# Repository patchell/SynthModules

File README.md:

# SynthModules
 Collection of Analog Synthesizer Modules

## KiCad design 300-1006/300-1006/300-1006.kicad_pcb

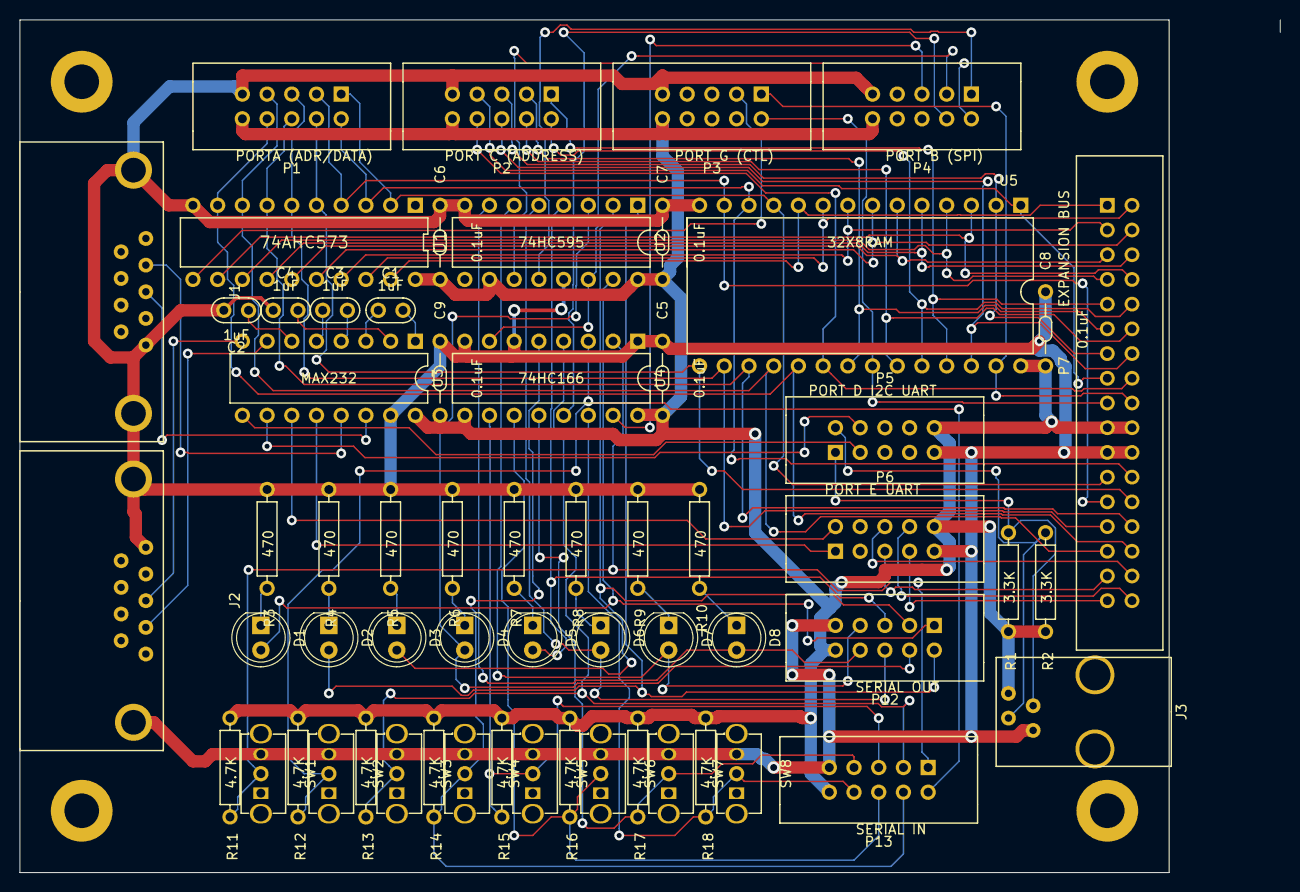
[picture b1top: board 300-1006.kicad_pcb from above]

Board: 2 copper layers, 129.5 x 87.6 mm, 64 parts (0 on the bottom side), 78 nets.

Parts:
C1, C2, C3, C4: 1uF; CAP-0.1
C5, C6, C7, C8, C9: 0.1uF; CAP-Bypass-0_3
D1, D2, D3, D4, D5, D6, D7, D8: LED; LED_5.0mm
J1: RS232 DTE MALE; DSUB-9P
J2: RS232 DCE FEM; DSUB-9S
J3: I2C; RJ9-PCB-Conn
P1: PORTA (ADR/DATA); IDC5x2_Vert
P2: PORT C (ADDRESS); IDC5x2_Vert
P3: PORT G (CTL); IDC5x2_Vert
P4: PORT B (SPI); IDC5x2_Vert
P5: PORT D I2C UART; IDC5x2_Vert
P6: PORT E UART; IDC5x2_Vert
P7: EXPANSION BUS; IDC_17x2
P8, P9, P10, P11: PAD; MountingHole_140
P12: SERIAL OUT; IDC5x2_Vert
P13: SERIAL IN; IDC5x2_Vert
R1, R2: 3.3K; AXIAL0_4
R3, R4, R5, R6, R7, R8, R9, R10: 470; AXIAL0_4
R11, R12, R13, R14, R15, R16, R17, R18: 4.7K; AXIAL0_4
SW1, SW2, SW3, SW4, SW5, SW6, SW7, SW8: SW-SPDT; SWITCH_SPDT-OS102011MS2QN1
U1: 74AHC573; DIP-20.3
U2: 74HC595; DIP-16
U3: MAX232; DIP-16
U4: 74HC166; DIP-16
U5: 32X8RAM; DIP28_6

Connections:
+5V0: C5.1, C6.1, C7.1, C8.1, C9.1, J3.4, P1.10, P2.10, P3.10, P4.10, P5.10, P6.10, P7.19, P7.20, P12.10, P13.10, R1.1, R2.1, R11.2, R12.2, R13.2, R14.2, R15.2, R16.2, R17.2, R18.2, U1.20, U2.10, U2.16, U3.16, U4.9, U4.16, U5.28
/A0: P7.1, U1.19, U5.10
/A1: P7.2, U1.18, U5.9
/A2: P7.3, U1.17, U5.8
/A3: P7.4, U1.16, U5.7
/A4: P7.5, U1.15, U5.6
/A5: P7.6, U1.14, U5.5
/A6: P7.7, U1.13, U5.4
/A7: P7.8, U1.12, U5.3
/A8: P2.1, P7.9, U5.25
/A9: P2.2, P7.10, U5.24
/A10: P2.3, P7.11, U5.21
/A11: P2.4, P7.12, U5.23
/A12: P2.5, P7.13, U5.2
/A13: P2.6, P7.14, U5.26
/A14: P2.7, P7.15, U5.1
/A15: P2.8, P7.16, U5.20
/AD0: P1.1, P7.23, U1.2, U5.11
/AD1: P1.2, P7.24, U1.3, U5.12
/AD2: P1.3, P7.25, U1.4, U5.13
/AD3: P1.4, P7.26, U1.5, U5.15
/AD4: P1.5, P7.27, U1.6, U5.16
/AD5: P1.6, P7.28, U1.7, U5.17
/AD6: P1.7, P7.29, U1.8, U5.18
/AD7: P1.8, P7.30, U1.9, U5.19
/ALE: P3.3, U1.11
/INT4: P6.5, P7.31
/INT5: P6.6, P7.32
/INT6: P6.7, P7.33
/INT7: P6.8, P7.34
/LOAD: P4.1, U2.12
/MISO: P4.4, U4.13
/MOSI: P4.3, U2.14, U4.7
/NRD: P3.2, P7.17, U5.22
/NWR: P3.1, P7.18, U5.27
/RXD0: J1.2, U3.13
/RXD0M: P6.1, U3.12
/RXD1: J2.3, U3.8
/RXD1M: P5.3, U3.9
/SCK: P4.2, U2.11
/SCL: J3.3, P5.1, R1.2
/SDA: J3.2, P5.2, R2.2
/SH_NLD: P4.5, U4.15
/SI0: P13.1, R11.1, SW1.2, U4.2
/SI1: P13.2, R12.1, SW2.2, U4.3
/SI2: P13.3, R13.1, SW3.2, U4.4
/SI3: P13.4, R14.1, SW4.2, U4.5
/SI4: P13.5, R15.1, SW5.2, U4.10
/SI5: P13.6, R16.1, SW6.2, U4.11
/SI6: P13.7, R17.1, SW7.2, U4.12
/SI7: P13.8, R18.1, SW8.2, U4.14
/SO0: D1.2, P12.1, U2.15
/SO1: D2.2, P12.2, U2.1
/SO2: D3.2, P12.3, U2.2
/SO3: D4.2, P12.4, U2.3
/SO4: D5.2, P12.5, U2.4
/SO5: D6.2, P12.6, U2.5
/SO6: D7.2, P12.7, U2.6
/SO7: D8.2, P12.8, U2.7
/TXD0: J1.3, U3.14
/TXD0M: P6.2, U3.11
/TXD1: J2.2, U3.7
/TXD1M: P5.4, U3.10
GND: C2.1, C4.2, C5.2, C6.2, C7.2, C8.2, C9.2, J1.0, J1.5, J2.0, J2.5, J3.1, P1.9, P2.9, P3.9, P4.9, P5.9, P6.9, P7.21, P7.22, P12.9, P13.9, R3.2, R4.2, R5.2, R6.2, R7.2, R8.2, R9.2, R10.2, SW1.3, SW2.3, SW3.3, SW4.3, SW5.3, SW6.3, SW7.3, SW8.3, U1.10, U2.8, U2.13, U3.15, U4.1, U4.6, U4.8, U5.14
unnamed: C1.1, U3.1
unnamed: C1.2, U3.3
unnamed: C2.2, U3.6
unnamed: C3.1, U3.4
unnamed: C3.2, U3.5
unnamed: C4.1, U3.2
unnamed: D1.1, R3.1
unnamed: D2.1, R4.1
unnamed: D3.1, R5.1
unnamed: D4.1, R6.1
unnamed: D5.1, R7.1
unnamed: D6.1, R8.1
unnamed: D7.1, R9.1
unnamed: D8.1, R10.1

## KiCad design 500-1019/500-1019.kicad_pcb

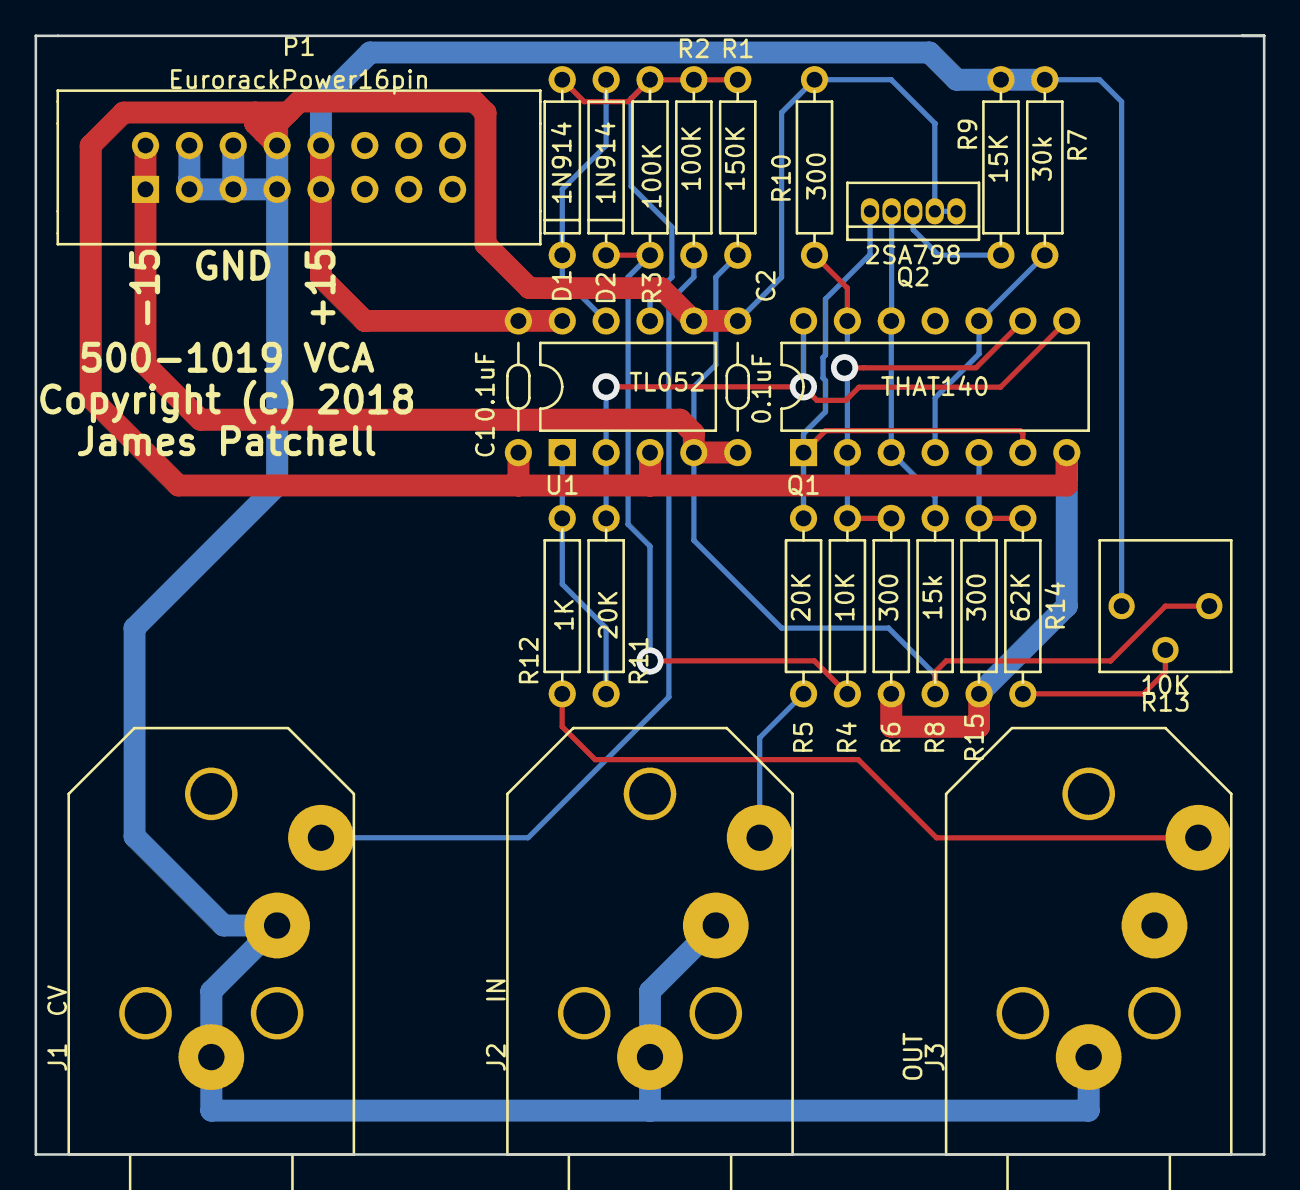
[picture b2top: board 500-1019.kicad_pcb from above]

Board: 2 copper layers, 71.1 x 64.8 mm, 26 parts (0 on the bottom side), 19 nets.

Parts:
C1, C2: 0.1uF; CAP-Bypass-0.3
D1, D2: 1N914; DIODE0.4
J1: CV; PHONE-SC112A
J2: IN; PHONE-SC112A
J3: OUT; PHONE-SC112A
P1: EurorackPower16pin; IDC8x2_Vert
Q1: THAT140; DIP-14.3
Q2: 2SA798
R1: 150K; AXIAL0_4
R2, R3: 100K; AXIAL0_4
R4: 10K; AXIAL0.4
R5, R11: 20K; AXIAL0.4
R6, R10, R15: 300; AXIAL0.4
R7: 30k; AXIAL0.4
R8: 15k; AXIAL0.4
R9: 15K; AXIAL0.4
R12: 1K; AXIAL0.4
R13: 10K; Trimpot
R14: 62K; AXIAL0.4
U1: TL052; DIP8.3

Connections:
+15V0: C1.1, P1.9, P1.10, R7.1, R9.1, R13.1, U1.8
-15V0: C2.1, P1.1, P1.2, R1.2, R8.2, R13.3, U1.4
/Vin: D2.1, R3.1, R4.2
GND: C1.2, C2.2, J1.1, J1.2, J2.1, J2.2, J3.1, P1.3, P1.4, P1.5, P1.6, P1.7, P1.8, Q1.7, Q2.4, Q2.5, R6.2, R10.2, R15.2, U1.3, U1.5
unnamed: D1.1, D2.2, U1.7
unnamed: D1.2, R1.1, R2.1, R3.2, U1.6
unnamed: J1.3, R2.2
unnamed: J2.3, R5.2
unnamed: J3.3, R12.1
unnamed: Q1.1, Q1.6, Q2.1, R5.1
unnamed: Q1.2, Q1.9, R4.1, R6.1
unnamed: Q1.5, R14.1, R15.1
unnamed: Q1.4, Q1.10, R7.2
unnamed: Q1.3, Q1.12, Q2.2, R8.1
unnamed: Q1.13, R10.1
unnamed: Q1.8, Q1.14, R11.2, U1.2
unnamed: Q2.3, R9.2
unnamed: R11.1, R12.2, U1.1
unnamed: R13.2, R14.2

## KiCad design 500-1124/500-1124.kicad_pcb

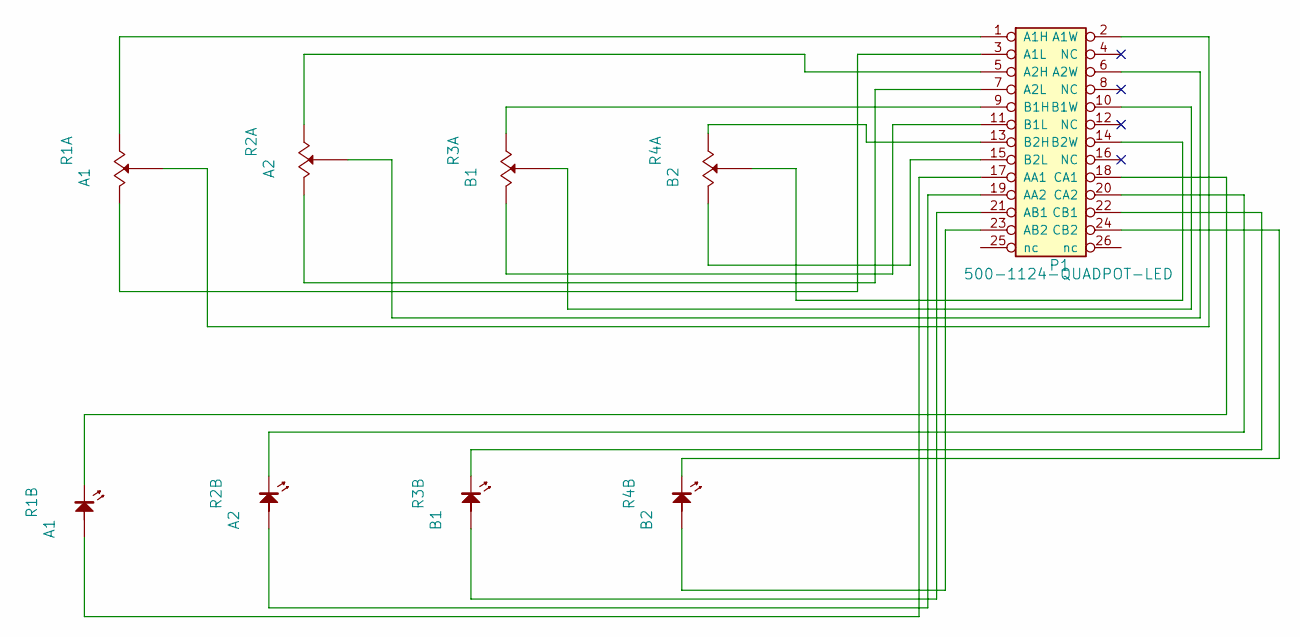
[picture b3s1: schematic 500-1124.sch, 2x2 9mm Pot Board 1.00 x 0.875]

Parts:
P1: 500-1124-QUADPOT-LED; IDC_Header_Straight_26pins
R1: A1; Alpha9mmPotWithLED
R2: A2; Alpha9mmPotWithLED
R3: B1; Alpha9mmPotWithLED
R4: B2; Alpha9mmPotWithLED

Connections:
unnamed: P1.1 (A1H), R1.1 (A)
unnamed: P1.2 (A1W), R1.2 (Wiper)
unnamed: P1.3 (A1L), R1.3 (B)
unnamed: P1.5 (A2H), R2.1 (A)
unnamed: P1.6 (A2W), R2.2 (Wiper)
unnamed: P1.7 (A2L), R2.3 (B)
unnamed: P1.9 (B1H), R3.1 (A)
unnamed: P1.10 (B1W), R3.2 (Wiper)
unnamed: P1.11 (B1L), R3.3 (B)
unnamed: P1.13 (B2H), R4.1 (A)
unnamed: P1.14 (B2W), R4.2 (Wiper)
unnamed: P1.15 (B2L), R4.3 (B)
unnamed: P1.17 (AA1), R1.5 (ANODE)
unnamed: P1.18 (CA1), R1.4 (CATHODE)
unnamed: P1.19 (AA2), R2.5 (ANODE)
unnamed: P1.20 (CA2), R2.4 (CATHODE)
unnamed: P1.21 (AB1), R3.5 (ANODE)
unnamed: P1.22 (CB1), R3.4 (CATHODE)
unnamed: P1.23 (AB2), R4.5 (ANODE)
unnamed: P1.24 (CB2), R4.4 (CATHODE)

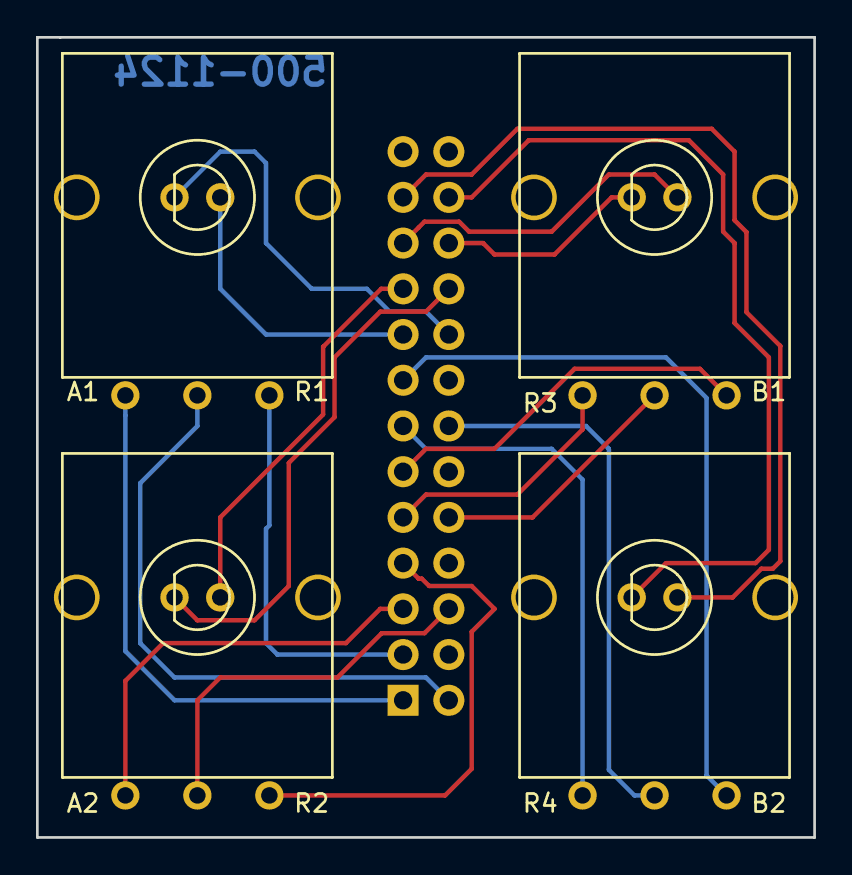
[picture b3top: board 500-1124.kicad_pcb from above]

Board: 2 copper layers, 43.2 x 44.5 mm, 5 parts (1 on the bottom side), 20 nets.

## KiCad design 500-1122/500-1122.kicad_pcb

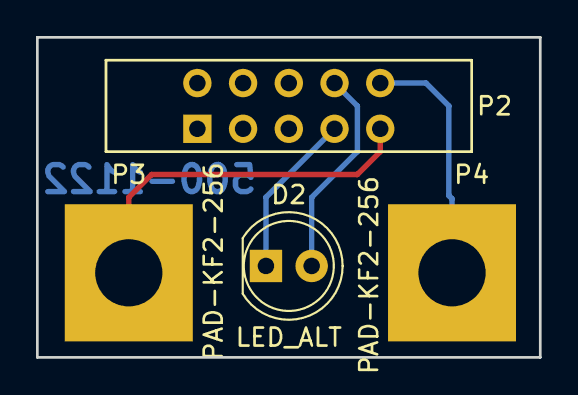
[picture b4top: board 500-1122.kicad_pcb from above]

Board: 2 copper layers, 27.9 x 17.8 mm, 4 parts (0 on the bottom side), 4 nets.

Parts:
D2: LED_ALT; LED_5.0mm
P2: 500-1121/2; IDC5x2_Vert
P3, P4: PAD-KF2-256; KF2-256-TerminalPad

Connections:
unnamed: D2.1, P2.7
unnamed: D2.2, P2.8
unnamed: P2.9, P3.1
unnamed: P2.10, P4.1

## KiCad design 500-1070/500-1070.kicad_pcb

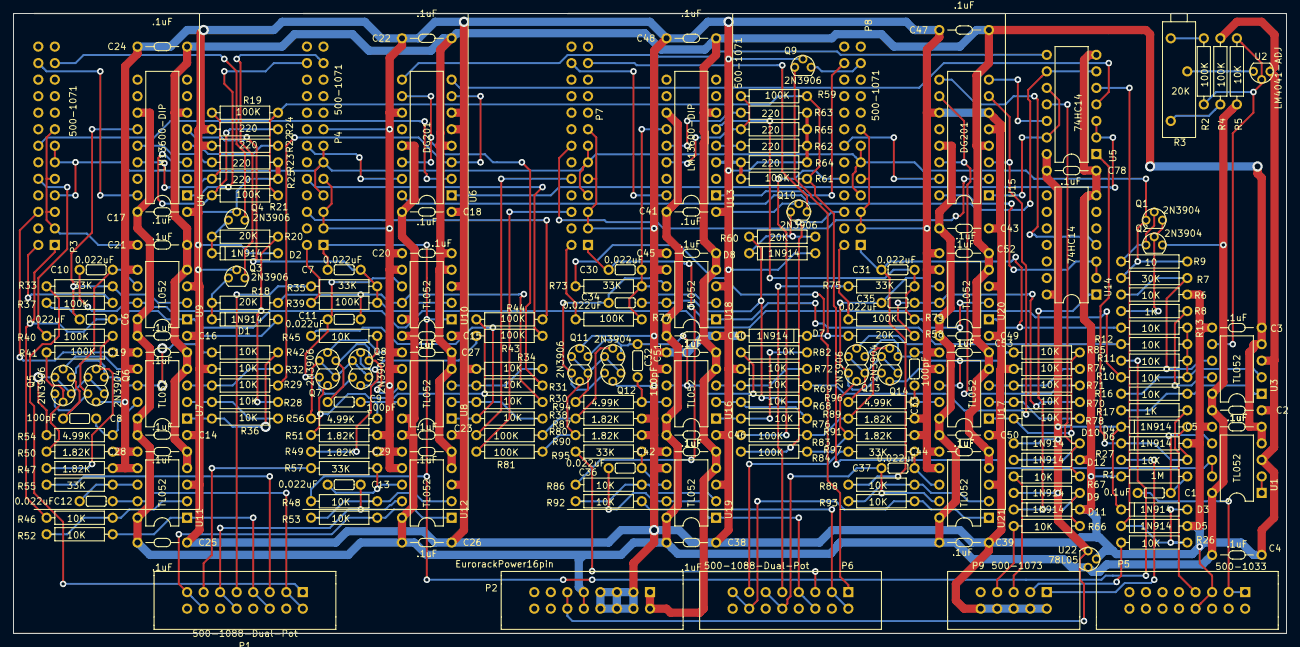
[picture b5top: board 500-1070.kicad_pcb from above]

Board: 2 copper layers, 195.6 x 95.2 mm, 206 parts (0 on the bottom side), 148 nets.

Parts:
C1: 0.1uF; CAP-GREENIE-0.2
C2, C3, C4, C5, C14, C15, C16, C17, C18, C19, C20, C21, C22, C23, C24, C25, C26, C27, C28, C29, C38, C39, C40, C41, C42, C43, C44, C45, C46, C47, C48, C49, C50, C51, C52, C53, C78: .1uF; CAP-Bypass-0.3
C6, C7, C10, C11, C12, C13, C30, C31, C34, C35, C36, C37: 0.022uF; CAP-GREENIE-0.2
C8, C9, C32, C33: 100pF; CAP-GREENIE-0.2
D1, D2, D3, D4, D5, D6, D7, D8, D9, D10, D11, D12: 1N914; DIODE0.4
P1, P6: 500-1088-Dual-Pot; IDC8x2_Vert
P2: EurorackPower16pin; IDC8x2_Vert
P3, P4, P7, P8: 500-1071; 500-1071-Footprint
P5: 500-1033; IDC8x2_Vert
P9: 500-1073; IDC5x2_Vert
Q1, Q2: 2N3904; TO92
Q3, Q4, Q9, Q10: 2N3906; TO92
Q5, Q7, Q11, Q13: 2N3906; DUAL_TO92
Q6, Q8, Q12, Q14: 2N3904; DUAL_TO92
R1: 1M; AXIAL0.4
R2, R4, R19, R21, R37, R39, R40, R41, R43, R44, R59, R61, R77, R79, R80, R81, R83, R84: 100K; AXIAL0.4
R3: 20K; Trimpot-3006
R5, R6, R10, R11, R12, R13, R16, R26, R27, R28, R29, R30, R31, R32, R34, R36, R38, R42, R45, R46, R48, R52, R53, R66, R67, R68, R69, R70, R71, R72, R74, R76, R78, R82, R85, R86, R88, R92, R93: 10K; AXIAL0.4
R7: 30K; AXIAL0.4
R8, R17: 1K; AXIAL0.4
R9: 10; AXIAL0.4
R18, R20, R58, R60: 20K; AXIAL0.4
R22, R23, R24, R25, R62, R63, R64, R65: 220; AXIAL0.4
R33, R35, R55, R57, R73, R75, R95, R97: 33K; AXIAL0.4
R47, R49, R50, R51, R87, R89, R90, R91: 1.82K; AXIAL0.4
R54, R56, R94, R96: 4.99K; AXIAL0.4
U1, U3, U7, U8, U9, U10, U11, U12, U16, U17, U18, U19, U20, U21: TL052; DIP8.3
U2: LM4041-ADJ; TO92
U4, U13: LM13600-DIP; DIP-16.3
U5, U14: 74HC14; DIP-14.3
U6, U15: DG201; DIP-16.3
U22: 78L05; TO92

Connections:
+5V0: C78.1, D3.1, D4.1, D9.1, D10.1, P2.11, P2.12, U5.14, U14.14, U22.1
+10: P3.7, P3.11, P3.13, P4.7, P4.11, P4.13, P7.7, P7.11, P7.13, P8.7, P8.11, P8.13, Q1.1, R7.1, R9.2
+15V0: C2.1, C4.1, C14.1, C15.1, C16.1, C17.1, C18.1, C23.1, C25.1, C26.1, C38.1, C39.1, C40.1, C41.1, C43.1, C46.1, C49.1, C50.1, P2.9, P2.10, Q2.3, R5.1, U1.8, U3.8, U4.11, U6.13, U7.8, U8.8, U9.8, U10.8, U11.8, U12.8, U13.11, U15.13, U16.8, U17.8, U18.8, U19.8, U20.8, U21.8, U22.3
-15V0: C3.1, C5.1, C19.1, C20.1, C21.1, C22.1, C24.1, C27.1, C28.1, C29.1, C42.1, C44.1, C45.1, C47.1, C48.1, C51.1, C52.1, C53.1, P2.1, P2.2, U1.4, U3.4, U4.6, U6.4, U7.4, U8.4, U9.4, U10.4, U11.4, U12.4, U13.6, U15.4, U16.4, U17.4, U18.4, U19.4, U20.4, U21.4
/Resonator_1/ATTACKa: P3.6, R41.1
/Resonator_1/ATTACKb: P4.6, R44.1
/Resonator_1/FH1a: P1.1, R33.2
/Resonator_1/FH1b: P1.9, R35.2
/Resonator_1/FH2a: P1.5, R55.1
/Resonator_1/FH2b: P1.13, R57.1
/Resonator_1/FW1a: C12.2, P1.2, P1.3, U11.7
/Resonator_1/FW1b: C13.2, P1.10, P1.11, U12.7
/Resonator_1/FW2a: P1.6, P1.7, R52.2, U11.1
/Resonator_1/FW2b: P1.14, P1.15, R53.2, U12.1
/Resonator_1/GATEa: P9.1, R27.1
/Resonator_1/GATEb: P9.3, R26.1
/Resonator_1/INa: R19.1, R21.1, R59.1, R61.1, U1.6, U1.7
/Resonator_1/LEDa: P3.23, Q4.3
/Resonator_1/LEDaK: P3.24, U4.16
/Resonator_1/LEDb: P4.23, Q3.3
/Resonator_1/LEDbK: P4.24, U4.1
/Resonator_1/OUTa: C6.2, P3.1, R10.1, R46.1, U9.1
/Resonator_1/OUTb: C7.2, P4.1, R11.1, R48.1, U10.1
/Resonator_1/RELEASEa: P3.10, R40.1
/Resonator_1/RELEASEb: P4.10, R43.1
/Resonator_1/RWa: P3.2, R37.2
/Resonator_1/RWb: P4.2, R39.2
/Resonator_1/SUSa: P3.14, U6.2
/Resonator_1/SUSb: P4.14, U6.15
/Resonator_2/ATTACKa: P7.6, R81.1
/Resonator_2/ATTACKb: P8.6, R84.1
/Resonator_2/FH1a: P6.1, R73.2
/Resonator_2/FH1b: P6.9, R75.2
/Resonator_2/FH2a: P6.5, R95.1
/Resonator_2/FH2b: P6.13, R97.1
/Resonator_2/FW1a: C36.2, P6.2, P6.3, U19.7
/Resonator_2/FW1b: C37.2, P6.10, P6.11, U21.7
/Resonator_2/FW2a: P6.6, P6.7, R92.2, U19.1
/Resonator_2/FW2b: P6.14, P6.15, R93.2, U21.1
/Resonator_2/GATEa: P9.5, R67.1
/Resonator_2/GATEb: P9.7, R66.1
/Resonator_2/LEDa: P7.23, Q10.3
/Resonator_2/LEDaK: P7.24, U13.16
/Resonator_2/LEDb: P8.23, Q9.3
/Resonator_2/LEDbK: P8.24, U13.1
/Resonator_2/OUTa: C30.2, P7.1, R12.1, R86.1, U18.1
/Resonator_2/OUTb: C31.2, P8.1, R13.1, R88.1, U20.1
/Resonator_2/RELEASEa: P7.10, R80.1
/Resonator_2/RELEASEb: P8.10, R83.1
/Resonator_2/RWa: P7.2, R77.2
/Resonator_2/RWb: P8.2, R79.2
/Resonator_2/SUSa: P7.14, U15.2
/Resonator_2/SUSb: P8.14, U15.15
GND: C2.2, C3.2, C4.2, C5.2, C14.2, C15.2, C16.2, C17.2, C18.2, C19.2, C20.2, C21.2, C22.2, C23.2, C24.2, C25.2, C26.2, C27.2, C28.2, C29.2, C38.2, C39.2, C40.2, C41.2, C42.2, C43.2, C44.2, C45.2, C46.2, C47.2, C48.2, C49.2, C50.2, C51.2, C52.2, C53.2, C78.2, D1.2, D2.2, D5.2, D6.2, D7.2, D8.2, D11.2, D12.2, P2.3, P2.4, P2.5, P2.6, P2.7, P2.8, P3.3, P3.5, P3.9, P3.15, P4.3, P4.5, P4.9, P4.15, P5.5, P5.8, P7.3, P7.5, P7.9, P7.15, P8.3, P8.5, P8.9, P8.15, P9.2, P9.4, P9.6, P9.8, P9.10, Q3.2, Q4.2, Q5.2, Q6.5, Q7.2, Q8.5, Q9.2, Q10.2, Q11.2, Q12.5, Q13.2, Q14.5, R1.2, R4.2, R6.2, R22.2, R23.2, R24.2, R25.2, R32.2, R34.2, R47.2, R49.2, R50.2, R51.2, R62.2, R63.2, R64.2, R65.2, R72.2, R74.2, R87.2, R89.2, R90.2, R91.2, U1.3, U2.1, U3.3, U5.7, U6.5, U6.6, U6.11, U7.5, U8.5, U9.3, U9.5, U10.3, U10.5, U11.3, U11.5, U12.3, U12.5, U14.7, U15.5, U15.6, U15.11, U16.5, U17.5, U18.3, U18.5, U19.3, U19.5, U20.3, U20.5, U21.3, U21.5, U22.2
unnamed: C1.1, P5.1, P5.3
unnamed: C1.2, R1.1, U1.5
unnamed: C6.1, R33.1, R37.1, U4.12, U9.2
unnamed: C7.1, R35.1, R39.1, U4.5, U10.2
unnamed: C8.1, Q5.3, Q6.3, R42.2, U7.6
unnamed: C8.2, R54.2, U7.7
unnamed: C9.1, Q7.3, Q8.3, R45.2, U8.6
unnamed: C9.2, R56.2, U8.7
unnamed: C10.1, Q5.6, Q6.6, U9.6
unnamed: C10.2, R20.1, R28.1, U9.7
unnamed: C11.1, Q7.6, Q8.6, U10.6
unnamed: C11.2, R18.1, R30.1, U10.7
unnamed: C12.1, R55.2, U11.6
unnamed: C13.1, R57.2, U12.6
unnamed: C30.1, R73.1, R77.1, U13.12, U18.2
unnamed: C31.1, R75.1, R79.1, U13.5, U20.2
unnamed: C32.1, Q11.3, Q12.3, R82.2, U16.6
unnamed: C32.2, R94.2, U16.7
unnamed: C33.1, Q13.3, Q14.3, R85.2, U17.6
unnamed: C33.2, R96.2, U17.7
unnamed: C34.1, Q11.6, Q12.6, U18.6
unnamed: C34.2, R60.1, R68.1, U18.7
unnamed: C35.1, Q13.6, Q14.6, U20.6
unnamed: C35.2, R58.1, R70.1, U20.7
unnamed: C36.1, R95.2, U19.6
unnamed: C37.1, R97.2, U21.6
unnamed: D1.1, Q3.1, R18.2
unnamed: D2.1, Q4.1, R20.2
unnamed: D3.2, D5.1, R26.2, U5.5
unnamed: D4.2, D6.1, R27.2, U5.1
unnamed: D7.1, Q9.1, R58.2
unnamed: D8.1, Q10.1, R60.2
unnamed: D10.2, D12.1, R67.2, U5.11
unnamed: D9.2, D11.1, R66.2, U14.1
unnamed: P5.7, R17.2
unnamed: Q1.2, Q2.1, R9.1
unnamed: Q1.3, Q2.2, R8.1
unnamed: Q5.1, Q5.4, Q6.1, Q6.4, R54.1
unnamed: Q5.5, R41.2, R50.1
unnamed: Q6.2, R40.2, R47.1
unnamed: Q7.1, Q7.4, Q8.1, Q8.4, R56.1
unnamed: Q7.5, R44.2, R51.1
unnamed: Q8.2, R43.2, R49.1
unnamed: Q11.1, Q11.4, Q12.1, Q12.4, R94.1
unnamed: Q11.5, R81.2, R90.1
unnamed: Q12.2, R80.2, R87.1
unnamed: Q13.1, Q13.4, Q14.1, Q14.4, R96.1
unnamed: Q13.5, R84.2, R91.1
unnamed: Q14.2, R83.2, R89.1
unnamed: R2.1, R5.2, U2.2, U3.5
unnamed: R2.2, R3.1
unnamed: R3.2, U2.3
unnamed: R3.3, R4.1
unnamed: R6.1, R7.2, U3.6
unnamed: R8.2, U3.7
unnamed: R10.2, R11.2, R12.2, R13.2, R16.1, U3.2
unnamed: R16.2, R17.1, U3.1
unnamed: R19.2, R25.1, U4.14
unnamed: R21.2, R24.1, U4.3
unnamed: R22.1, U4.4
unnamed: R23.1, U4.13
unnamed: R28.2, R36.1, U7.2
unnamed: R29.1, U6.3, U6.7
unnamed: R29.2, R32.1, U7.3
unnamed: R30.2, R38.1, U8.2
unnamed: R31.1, U6.10, U6.14
unnamed: R31.2, R34.1, U8.3
unnamed: R36.2, R42.1, U7.1
unnamed: R38.2, R45.1, U8.1
unnamed: R46.2, R52.1, U11.2
unnamed: R48.2, R53.1, U12.2
unnamed: R59.2, R65.1, U13.14
unnamed: R61.2, R64.1, U13.3
unnamed: R62.1, U13.4
unnamed: R63.1, U13.13
unnamed: R68.2, R76.1, U16.2
unnamed: R69.1, U15.3, U15.7
unnamed: R69.2, R72.1, U16.3
unnamed: R70.2, R78.1, U17.2
unnamed: R71.1, U15.10, U15.14
unnamed: R71.2, R74.1, U17.3
unnamed: R76.2, R82.1, U16.1
unnamed: R78.2, R85.1, U17.1
unnamed: R86.2, R92.1, U19.2
unnamed: R88.2, R93.1, U21.2
unnamed: U1.1, U1.2
unnamed: U5.2, U5.3, U6.1
unnamed: U5.4, U6.8
unnamed: U5.6, U5.9, U6.16
unnamed: U5.8, U6.9
unnamed: U14.2, U14.3, U15.16
unnamed: U14.4, U15.9
unnamed: U5.10, U5.13, U15.1
unnamed: U5.12, U15.8

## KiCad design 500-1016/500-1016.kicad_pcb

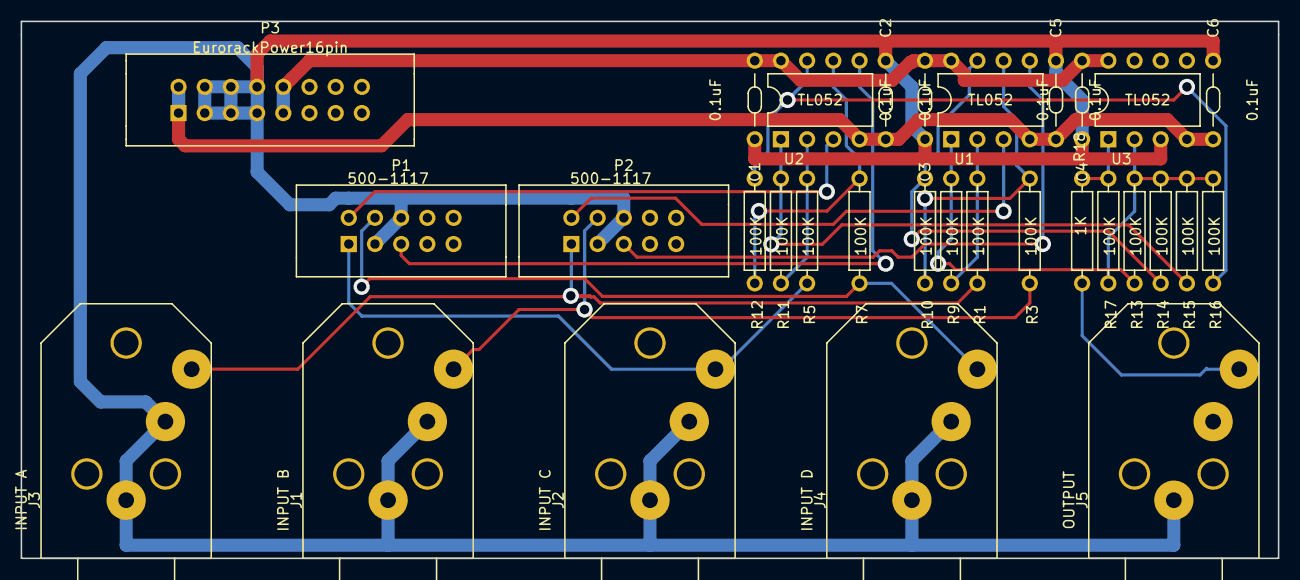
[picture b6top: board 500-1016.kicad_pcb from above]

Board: 2 copper layers, 121.9 x 52.1 mm, 31 parts (0 on the bottom side), 22 nets.

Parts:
C1, C2, C3, C4, C5, C6: 0.1uF; CAP-Bypass-0.3
J1: INPUT B; PHONE-SC112A
J2: INPUT C; PHONE-SC112A
J3: INPUT A; PHONE-SC112A
J4: INPUT D; PHONE-SC112A
J5: OUTPUT; PHONE-SC112A
P1, P2: 500-1117; IDC5x2_Vert
P3: EurorackPower16pin; IDC8x2_Vert
R1, R3, R5, R7, R9, R10, R11, R12, R13, R14, R15, R16, R17: 100K; AXIAL0.4
R18: 1K; AXIAL0.4
U1, U2, U3: TL052; DIP8.3

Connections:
+15V0: C1.1, C3.1, C4.1, P3.9, P3.10, U1.8, U2.8, U3.8
-15V0: C2.1, C5.1, C6.1, P3.1, P3.2, U1.4, U2.4, U3.4
GND: C1.2, C2.2, C3.2, C4.2, C5.2, C6.2, J1.1, J1.2, J2.1, J2.2, J3.1, J3.2, J4.1, J4.2, J5.1, P1.3, P1.6, P2.3, P2.6, P3.3, P3.4, P3.5, P3.6, P3.7, P3.8, U3.3
unnamed: J1.3, P2.4, R3.1
unnamed: J2.3, P1.1, R5.1
unnamed: J3.3, P2.1, R1.1
unnamed: J4.3, P1.4, R7.1
unnamed: J5.3, R18.2
unnamed: P1.2, U2.3
unnamed: P1.5, U2.5
unnamed: P2.2, U1.3
unnamed: P2.5, U1.5
unnamed: R1.2, R9.1, U1.2
unnamed: R3.2, R10.1, U1.6
unnamed: R10.2, R14.1, U1.7
unnamed: R5.2, R11.1, U2.2
unnamed: R11.2, R15.1, U2.1
unnamed: R7.2, R12.1, U2.6
unnamed: R12.2, R16.1, U2.7
unnamed: R9.2, R13.1, U1.1
unnamed: R13.2, R14.2, R15.2, R16.2, R17.1, U3.2
unnamed: R17.2, R18.1, U3.1

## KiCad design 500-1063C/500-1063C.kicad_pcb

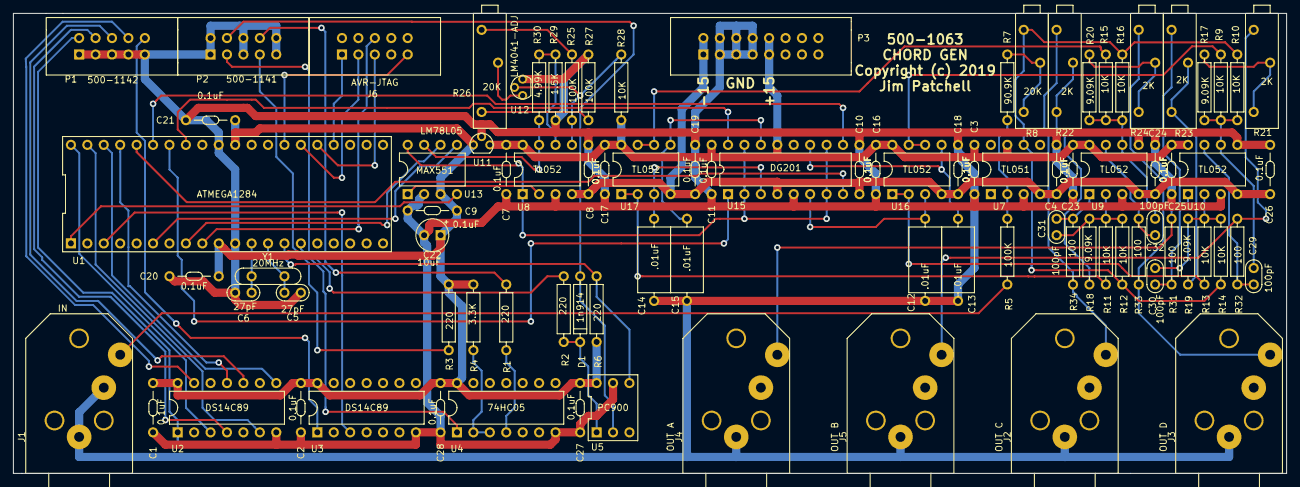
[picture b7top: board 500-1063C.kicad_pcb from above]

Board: 2 copper layers, 196.8 x 71.1 mm, 92 parts (0 on the bottom side), 73 nets.

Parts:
C1, C2, C3, C4, C7, C8, C9, C10, C11, C16, C17, C18, C19, C20, C21, C23, C24, C25, C26, C27, C28: 0.1uF; CAP-Bypass-0_3
C5, C6: 27pF; CAP-0.1
C12, C13, C14, C15: .01uF; CAP-AXIAL-0.5x0.2
C22: 10uF; Cap-Pol-Rad-0.2_0.1
C29, C30, C31, C32: 100pF; CAP-0.1
D1: 1n914; DIODE0.4
J1: IN; PHONE-SC112A
J2: OUT C; PHONE-SC112A
J3: OUT D; PHONE-SC112A
J4: OUT A; PHONE-SC112A
J5: OUT B; PHONE-SC112A
J6: AVR-JTAG; IDC5x2_Vert
P1: 500-1142; IDC5x2_Vert
P2: 500-1141; IDC5x2_Vert
P3: EurorackPower16pin; IDC8x2_Vert
R1, R2, R3, R6: 220; AXIAL0_4
R4: 3.3K; AXIAL0_4
R5, R25, R27: 100K; AXIAL0_4
R7: 90.9K; AXIAL0_4
R8, R26: 20K; Trimpot-3006
R9, R10, R11, R12, R13, R14, R15, R16, R28: 10K; AXIAL0_4
R17, R18, R19, R20: 9.09K; AXIAL0_4
R21, R22, R23, R24: 2K; Trimpot-3006
R29: 1.5K; AXIAL0_4
R30: 4.99K; AXIAL0_4
R31, R32, R33, R34: 100; AXIAL0_4
U1: ATMEGA1284; DIP-40
U2, U3: DS14C89; DIP-14
U4: 74HC05; DIP-14
U5: PC900; DIP-6
U7: TL051; DIP8
U8, U9, U10, U16, U17: TL052; DIP8
U11: LM78L05; TO92
U12: LM4041-ADJ; TO92
U13: MAX551; DIP8
U15: DG201; DIP16.3
Y1: 20MHz; XTAL

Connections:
+15V0: C3.1, C7.1, C11.1, C16.1, C17.1, C23.1, C25.1, P3.9, P3.10, R28.1, U7.7, U8.8, U9.8, U10.8, U11.3, U15.13, U16.8, U17.8
-15V0: C4.1, C8.1, C10.1, C18.1, C19.1, C24.1, C26.1, P3.1, P3.2, U7.4, U8.4, U9.4, U10.4, U15.4, U16.4, U17.4
/AVR/A: U1.40, U2.3
/AVR/B: U1.39, U2.6
/AVR/C: U1.38, U2.8
/AVR/D: U1.37, U2.11
/AVR/GATE: U1.3, U3.3
/AVR/MIDI_IN: R6.2, U1.14, U5.4
/AVR/MIDI_OUT: U1.15, U4.1
/SampleHold/SA: U1.36, U15.8
/SampleHold/SB: U1.35, U15.9
/SampleHold/SC: U1.34, U15.1
/SampleHold/SD: U1.33, U15.16
/SampleHold/VA: R13.1, U16.1, U16.2
/SampleHold/VB: R9.1, U16.6, U16.7
/SampleHold/VC: R11.1, U17.1, U17.2
/SampleHold/VD: R15.1, U17.6, U17.7
/SampleHold/VIN: U8.1, U13.8, U15.2, U15.7, U15.10, U15.15
GND: C1.2, C2.2, C3.2, C4.2, C5.2, C6.2, C7.2, C8.2, C9.2, C10.2, C11.2, C12.2, C13.2, C14.2, C15.2, C16.2, C17.2, C18.2, C19.2, C20.2, C21.2, C22.2, C23.2, C24.2, C25.2, C26.2, C27.2, C28.2, J1.1, J1.2, J2.1, J3.1, J4.1, J5.1, P1.1, P1.3, P1.5, P1.7, P1.9, P2.1, P2.2, P2.5, P2.6, P2.9, P2.10, P3.3, P3.4, P3.5, P3.6, P3.7, P3.8, R27.2, R29.2, U1.11, U1.31, U2.7, U3.7, U4.7, U5.5, U7.3, U8.3, U9.3, U9.5, U10.3, U10.5, U11.2, U12.3, U13.2, U15.5
unnamed: C5.1, U1.13, Y1.1
unnamed: C6.1, U1.12, Y1.2
unnamed: C12.1, U15.6, U16.3
unnamed: C13.1, U15.11, U16.5
unnamed: C14.1, U15.3, U17.3
unnamed: C15.1, U15.14, U17.5
unnamed: C29.1, R9.2, R10.2, R17.1, U10.6
unnamed: C29.2, R32.1, U10.7
unnamed: C30.1, R13.2, R14.2, R19.1, U10.2
unnamed: C30.2, R31.1, U10.1
unnamed: C31.1, R11.2, R12.2, R18.1, U9.2
unnamed: C31.2, R34.1, U9.1
unnamed: C32.1, R15.2, R16.2, R20.1, U9.6
unnamed: C32.2, R33.1, U9.7
unnamed: D1.1, R2.2, U5.1
unnamed: D1.2, P2.4, U5.2
unnamed: J1.3, R5.1
unnamed: J2.3, R22.1, R34.2
unnamed: J3.3, R24.1, R33.2
unnamed: J4.3, R23.1, R31.2
unnamed: J5.3, R21.1, R32.2
unnamed: J6.1, U1.24
unnamed: J6.3, U1.26
unnamed: J6.5, U1.25
unnamed: J6.6, U1.9
unnamed: J6.9, U1.27
unnamed: P1.2, U2.1
unnamed: P1.4, U2.4
unnamed: P1.6, U2.10
unnamed: P1.8, U2.13
unnamed: P1.10, U3.1
unnamed: P2.3, R2.1
unnamed: P2.7, R3.1
unnamed: P2.8, R1.1
unnamed: R1.2, U4.4
unnamed: R4.2, U4.2, U4.3
unnamed: R5.2, R7.1, U7.2
unnamed: R7.2, R8.2, R8.3
unnamed: R8.1, R10.1, R12.1, R14.1, R16.1, U7.6
unnamed: R17.2, R21.2, R21.3
unnamed: R18.2, R22.2, R22.3
unnamed: R19.2, R23.2, R23.3
unnamed: R20.2, R24.2, R24.3
unnamed: R25.1, R28.2, U8.5, U12.2
unnamed: R25.2, R26.1
unnamed: R26.2, U12.1
unnamed: R26.3, R27.1
unnamed: R29.1, R30.1, U8.6
unnamed: R30.2, U8.7, U13.7
unnamed: U1.1, U13.4
unnamed: U1.6, U13.5
unnamed: U1.8, U13.6
unnamed: U8.2, U13.1
VCC: C1.1, C2.1, C9.1, C20.1, C21.1, C22.1, C27.1, C28.1, R3.2, R4.1, R6.1, U1.10, U1.30, U2.14, U3.14, U4.14, U5.6, U11.1, U13.3

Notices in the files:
500-1007/500-1007/500-1007.kicad_pcb:
Copyright (c) 2018 James Patchell
500-1063C/500-1063C.kicad_pcb:
Copyright (c) 2019
